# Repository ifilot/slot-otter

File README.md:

# Slot-otter

An 8-bit ISA card for accessing FAT16- or FAT32-formatted SD cards under MS-DOS.

Slot-otter lets a DOS PC use an SD card as an ordinary drive. Fill the card
with files on a modern computer, insert it into your vintage PC, and copy or
run them from DOS.

Both boards are **fully supported and functionally equivalent**: **Slot-otter
Classic** (the original discrete-logic board) and **Slot-otter Forge** (the CPLD
board) use the same OTTERSD driver and
provide the same DOS drive functionality. Owners of the original board can
use the current driver and follow the setup instructions below.

| [Slot-otter Classic](pcb/release/README.md) | [Slot-otter Forge](pcb/cpld/README.md) |
| :---: | :---: |
|  |  |
|  |  |
|  |  |

Click a preview to view the full-resolution image.

[Explore Classic and Forge in the interactive 3D viewer](https://ifilot.github.io/slot-otter/) — rotate and zoom each card in your browser.

A working setup has three parts:

- the **Slot-otter card** in a free 8-bit ISA slot;
- the **OTTERSD driver** on the PC's hard drive, loaded at startup;
- an **SD card** with a FAT16 or FAT32 file system.

## Contents

- [How it works](#how-it-works)
- [Requirements](#requirements)
- [Getting started](#getting-started)
  - [1. Set the port address](#1-set-the-port-address)
  - [2. Download the driver](#2-download-the-driver)
  - [3. Prepare an SD card](#3-prepare-an-sd-card)
  - [4. Install and load OTTERSD](#4-install-and-load-ottersd)
- [Using the card](#using-the-card)
  - [Changing or removing the SD card](#changing-or-removing-the-sd-card)
  - [Freeing memory for games](#freeing-memory-for-games)
  - [Write checks and read-only mode](#write-checks-and-read-only-mode)
  - [Browsing files with Nightwatch](#browsing-files-with-nightwatch)
- [Performance](#performance)
- [Hardware](#hardware)
- [Development](#development)
- [License](#license)

## How it works

`OTTERSD` is the DOS driver for Slot-otter. It is usually started from
`AUTOEXEC.BAT`. It talks to the card over the ISA bus, reads the FAT16 or FAT32
file system on the SD card, and gives the card an ordinary drive letter such
as `S:`. From then on, DIR, COPY, XCOPY, games and other DOS programs use the
card like any other drive and never need to know it is an SD card.

A driver is needed because, on its own, MS-DOS can only use the storage the
PC's BIOS already supports, which means floppy drives and hard disks. Any
other storage device needs a small program that stays in memory and turns DOS
requests such as "open this file" or "list this directory" into commands the
hardware understands. CD-ROM drives are the familiar example. Before a `D:`
drive appears, `CONFIG.SYS` has to load the manufacturer's CD-ROM driver and
`AUTOEXEC.BAT` has to run `MSCDEX`. `OTTERSD` does both of those jobs in a single
program.

## Requirements

Check these before you start. The driver refuses cards or file systems it
cannot handle safely.

- **PC:** an 8088/8086 or later processor and a free 8-bit ISA slot.
- **DOS:** MS-DOS or PC-DOS 3.1 through 6.x.
- **Memory:** about 42 KiB of conventional memory while the driver is loaded.
  No EMS or XMS is needed.
- **SD card:** SDHC or SDXC, at least 501 MiB. Older SDSC cards (2 GB and
  smaller) are not supported.
- **File system:** FAT16 or FAT32 with standard 512-byte sectors on an MBR
  partition. FAT12, exFAT, GPT and extended partitions are not supported.
- **File names:** the usual DOS limit of eight characters for the name and
  three for the extension, such as `DUNE2.EXE`.

## Getting started

Setting up Slot-otter for the first time takes four steps. The first is done
on the card before it goes into the PC, the third on a modern computer, and
the rest under DOS.

1. Set the card's port address and install it in the PC.
2. Download the driver and copy it to the DOS hard drive.
3. Write an empty FAT16 or FAT32 image to an SD card and add your files.
4. Install and load OTTERSD.

### 1. Set the port address

The PC talks to expansion cards through I/O ports, small numbered addresses
that each card listens on. Slot-otter occupies four consecutive ports. The
driver needs to know where they start, and no other card in the PC may use
the same ones.

The base address is set with the 8-position DIP switch labelled **ADDR SEL**
(SW1). Each switch stands for one value. Switches that are ON add their
values together to give the base address; switches that are OFF add nothing.

| Switch | 1 | 2 | 3 | 4 | 5 | 6 | 7 | 8 |
| --- | --- | --- | --- | --- | --- | --- | --- | --- |
| Value (hex) | 200 | 100 | 80 | 40 | 20 | 10 | 8 | 4 |
| **330h** (default) | ON | ON | OFF | OFF | ON | ON | OFF | OFF |
| **300h** | ON | ON | OFF | OFF | OFF | OFF | OFF | OFF |

For example, 330h = 200h + 100h + 20h + 10h, so switches 1, 2, 5 and 6 are ON.
The examples in this README and the driver documentation use 330h. Choose any
free address from 100h to 3FCh. Sound cards often use 330h for their MIDI
port, so pick another address, such as 300h, if your PC has one. Whatever you
choose, pass the same value to the driver with `/PORT:` in
[step 4](#4-install-and-load-ottersd).

With the PC switched off, insert the card into a free 8-bit ISA slot.

### 2. Download the driver

The driver is distributed as a ZIP for copying with a modern PC, as a bare
executable, and as floppy images for PCs that only have a floppy drive. Get
the [latest release](https://github.com/ifilot/slot-otter/releases/latest):

- [OTTERSD-DOS.zip](https://github.com/ifilot/slot-otter/releases/latest/download/OTTERSD-DOS.zip): driver, instructions and license.
- [OTTERSD.EXE](https://github.com/ifilot/slot-otter/releases/latest/download/OTTERSD.EXE): driver executable.
- [floppy_360k.img](https://github.com/ifilot/slot-otter/releases/latest/download/floppy_360k.img): 360 KiB, 5.25-inch DD.
- [floppy_720k.img](https://github.com/ifilot/slot-otter/releases/latest/download/floppy_720k.img): 720 KiB, 3.5-inch DD.
- [floppy_1440k.img](https://github.com/ifilot/slot-otter/releases/latest/download/floppy_1440k.img): 1.44 MiB, 3.5-inch HD.
- [SHA256.TXT](https://github.com/ifilot/slot-otter/releases/latest/download/SHA256.TXT): checksums for checking that downloads are intact.

The floppy images contain the driver, user instructions, a configuration
example and license. They are not boot disks.
Write them to physical floppies or use GoTek,
[BitstreamBeaver](https://github.com/ifilot/bitstream-beaver) or FlashFloppy.

### 3. Prepare an SD card

The easiest way to get a card in the right format is to write one of the
ready-made images to it on a modern PC. Both images contain an **empty,
formatted partition** with no files or folders. After writing one, copy your
files onto the card with the same PC.

**Recommended: [500 MiB FAT16, 16 KiB clusters](https://github.com/ifilot/slot-otter/releases/latest/download/OTTERSD-FAT16-500MiB.zip).**
This gives a useful balance of storage space and write speed. A cluster is
the unit of space the card assigns to a file. Larger clusters mean less
bookkeeping when growing a file, although small files take up more space.

An alternative [500 MiB FAT32 image with 4 KiB clusters](https://github.com/ifilot/slot-otter/releases/latest/download/OTTERSD-FAT32-500MiB.zip)
is also available.

Extract the ZIP and write its IMG to the **entire card**. This replaces existing
partitions and files: back up first and select the correct device. Do not copy
the IMG as a file or reformat the card afterwards. The image occupies 501 MiB,
including a small area before the 500 MiB partition. On a larger card, the
remaining space is unused by this image. These images hold your files; they
do not boot DOS.

A card that is already formatted FAT16 or FAT32 and meets the
[requirements](#requirements) can also be used without writing an image.

### 4. Install and load OTTERSD

The driver is copied to the hard drive and started like any other DOS program.
It must not be loaded from the SD drive it provides.

Copy OTTERSD.EXE to a directory on your DOS hard drive, such as `C:\OTTERSD`.
Choose an unused drive letter; this example uses `S:`. Add `LASTDRIVE=S` to
CONFIG.SYS (or keep an existing value of S or later), then reboot, insert the
SD card and load:

```dos
C:\OTTERSD\OTTERSD /DRIVE:S /PORT:330 /RW
```

The DOS screenshots on this page are illustrative drafts using the driver's
messages. Timing and resident-memory figures are examples, not hardware measurements.
The driver prints its version and a message before lengthy work. Console
commands also show percentage progress while comparing FAT copies; wait for
the final success message before using or removing the card. Redirected
output keeps plain status messages without the animated percentage.

`/PORT:330` must match the DIP-switch setting from
[step 1](#1-set-the-port-address). `/RW` enables writing with read-back checks.
Omit it or use `/RO` for read-only access. Once the driver reports that the
card is mounted, you can use commands such as `DIR S:\`.

Add the loading command to AUTOEXEC.BAT if you want it to run at startup.
Run OTTERSD as a program; do not add it as a `DEVICE=` line in CONFIG.SYS.
See the [installation guide](driver/docs/INSTALLATION.md) for the full setup
and available options.

## Using the card

Once loaded, the SD drive behaves like any other DOS drive. A few things
differ from a fixed hard disk, mainly because the card can be removed and the
driver can be unloaded.

### Changing or removing the SD card

**Always unmount before removing a card, and mount again after inserting one.**
Treat this like safely ejecting a card on your modern PC. DOS programs and
the driver can keep file data and information about the card in memory.
Removing or swapping a mounted card can lose changes or cause the driver
to use information belonging to the previous card, risking file corruption.

1. Finish copying and close any programs using the SD card. Return to a
   drive other than the SD card, such as `C:`.
2. Run `C:\OTTERSD\OTTERSD /UNMOUNT`. **Wait for it to succeed before
   removing the card.** If it reports an error, leave the card inserted
   and resolve the error first.
3. Remove the card and insert the card you want to use.
4. Run `C:\OTTERSD\OTTERSD /MOUNT` and wait for it to succeed before
   accessing the SD drive again.

Follow these steps even when reinserting the same card, especially after
changing its contents on another computer. Unmounting leaves the driver
loaded, so you do not need to reboot to change cards.

| Unmount before removing the card | Mount after inserting the card |
| :---: | :---: |
|  |  |

### Freeing memory for games

Some games need every kilobyte of conventional memory. The driver can be
removed from memory without rebooting: close programs using the SD card,
switch to your hard drive and run `C:\OTTERSD\OTTERSD /UNLOAD`. Run the
loading command again to bring the SD drive back.

### Write checks and read-only mode

With `/RW`, every block written to the card is read back and checked before
the write is reported as successful. With `/RO`, or without either option,
the card is mounted read-only and nothing on it can be changed. The access
mode is fixed when the driver is loaded; reboot to change it.

### Browsing files with Nightwatch

For browsing and copying files, we recommend
[Nightwatch](https://github.com/ifilot/nightwatch) together with OTTERSD.
Nightwatch is a separate project and is not bundled in these downloads.

## Performance

File-copy tests on an **80286 running at 20 MHz** gave these results:

| Direction | FAT16 card | FAT32 card |
| --- | --- | --- |
| To the SD card | 15 KiB/s | 10 KiB/s |
| From the SD card | 38 KiB/s | 38 KiB/s |

These are measured file-transfer speeds, not guaranteed speeds for every
system or card. FAT16 was faster when writing in these tests; reading was
equally fast with both formats. Speeds also depend on the CPU, the ISA bus
and the disk being copied to or from.

## Hardware

Slot-otter has two supported, functionally equivalent board designs:
the [Slot-otter Classic](pcb/release/README.md) discrete-logic board and
[Slot-otter Forge](pcb/cpld/README.md) CPLD board. Both use the same OTTERSD driver,
I/O port settings and SD card formats, including read and write support.

Classic implements the interface with discrete logic chips.
On Forge, an ATF1504AS implements the interface logic, with an external 74HCT688
comparing address lines A2 to A9 against the DIP-switch setting.

The hardware documentation includes KiCad sources, the bill of materials,
assembly positions, fabrication files and CPLD programming instructions.
Review the manufacturing reports, bring-up checks and timing limits before
building or using this revision.

Use the hardware files for your board: Classic and Forge have
different fabrication files and pinouts. The earlier
[prototype sources](pcb/prototype/README.md) are also retained.

## Development

The [driver documentation](driver/README.md) covers the source code, build
instructions and regression tests. The driver is built with Turbo C 2.0 and
TASM 2. [DOSBox-VirtIsa](https://github.com/ifilot/dosbox-virtisa) provides an
emulated ISA interface for development and testing.

See the [release history](CHANGELOG.md) for changes between versions.

## License

Slot-otter is certified open source hardware by the
[Open Source Hardware Association](https://certification.oshwa.org/nl000046.html)
under UID NL000046.

Project-authored hardware and mechanical designs use CERN-OHL-S-2.0;
software and CPLD logic use GPL-3.0-or-later; documentation uses CC-BY-SA-4.0.
See [licensing scope and full texts](LICENSE.md) for details and third-party
exceptions. Bundled Borland tools retain their proprietary terms.

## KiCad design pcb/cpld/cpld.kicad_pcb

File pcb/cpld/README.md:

# Slot-otter Forge

Forge is the CPLD-based Slot-otter board. Revision 1.0 uses an ATF1504AS
in a PLCC44 socket and the reassigned pinout in [logic/README.txt](logic/README.txt).
Do not use this programming image with an earlier PCB pinout.

## Design sources and licenses

Open `cpld.kicad_pro` in KiCad 10. The schematic is `cpld.kicad_sch` and the
PCB is `cpld.kicad_pcb`. Project libraries are registered through `fp-lib-table`
and `sym-lib-table`, with their files under `components/`.

Project-authored hardware uses CERN-OHL-S-2.0, software and CPLD logic use
GPL-3.0-or-later, and documentation uses CC-BY-SA-4.0. See the repository
[licensing statement](../../LICENSE.md) and [full license texts](../../LICENSES/).
The source location is https://github.com/ifilot/slot-otter .

The original discrete-logic board, [Slot-otter Classic](../release/README.md), remains fully supported
and is functionally equivalent to this board, using the same OTTERSD driver
and setup instructions. Its component references, manufacturing files and
pinouts differ from this board's. The earlier
[prototype sources](../prototype/README.md) are also retained.

## Manufacturing and assembly

- [Schematic PDF](cpld.pdf) and [SVG](cpld.svg).
- [Bill of materials](production/bom.csv), including schematic supplier fields and datasheet links.
- [Placement positions](production/positions.csv), in millimetres, and [assembly references](production/designators.csv).
- [Gerbers and drill files](GERBERS/), also available as a [fabrication ZIP](GERBERS/cpld.zip).
- [Generation manifest](production/manifest.json), [DRC](production/drc.json) and [ERC](production/erc.json).

Check `manufacturing_ready` and the reports before ordering. A generated export
is not manufacturing approval. A supplier field copied from the schematic is
not a purchasing validation; verify the exact package and part before assembly.
U1 needs both the ATF1504AS PLCC44 device and a compatible through-hole
PLCC44 socket. J2 is the integral ISA edge connector, not a separately
purchased connector. The bracket [STL sources](../../bracket/README.md) were authored as meshes for
earlier cards; check mechanical fit before using them with the CPLD layout.

Regenerate the outputs with KiCad 10 installed:

```sh
python3 pcb/cpld/export.py
```

Use `--kicad-cli /path/to/kicad-cli` when the executable is not on PATH.
The exporter refills and saves PCB copper zones, runs DRC/ERC, exports the
current schematic and board, rebuilds the fabrication ZIP, and records source
hashes. It exports both board sides in the placement CSV; configure your assembler's origin and rotation
conventions before submitting it. The `.dsn` and `.ses` files are historical
routing snapshots, not revision 1.0 manufacturing inputs.

## CPLD build and bring-up

The [CUPL source](logic/slototter.pld), [build script](logic/build.cmd),
[functional-vector generator](logic/generate_vectors.py) and
[pinout and timing documentation](logic/README.txt) are the editable logic sources.
Run `logic/build.cmd test` on Windows with WinCUPL installed to compile, fit and
simulate; then run `logic/build.cmd` for an image without simulation vectors.
Generated programming files are under `logic/build/` and are ignored by Git.

The revision 1.0 board has no on-board JTAG connector; its JTAG pads are
unconnected. Program the CPLD in a compatible external PLCC44 adapter or
fixture before inserting it into U1's socket. Use a programmer supporting
ATF1504AS and the target's voltage; follow its adapter pinout and power
instructions. The reserved PLCC44 JTAG pins are 7 TDI, 13 TMS, 32 TCK and
38 TDO. Program the newly generated `logic/build/slototter.jed`, then use
the programmer's verify operation. Programmer-specific commands depend on
the selected programmer. Disconnect power before inserting or removing U1.
Follow the bring-up checks and timing limits in the logic
README before using the [DOS driver](../../driver/README.md) on this revision.

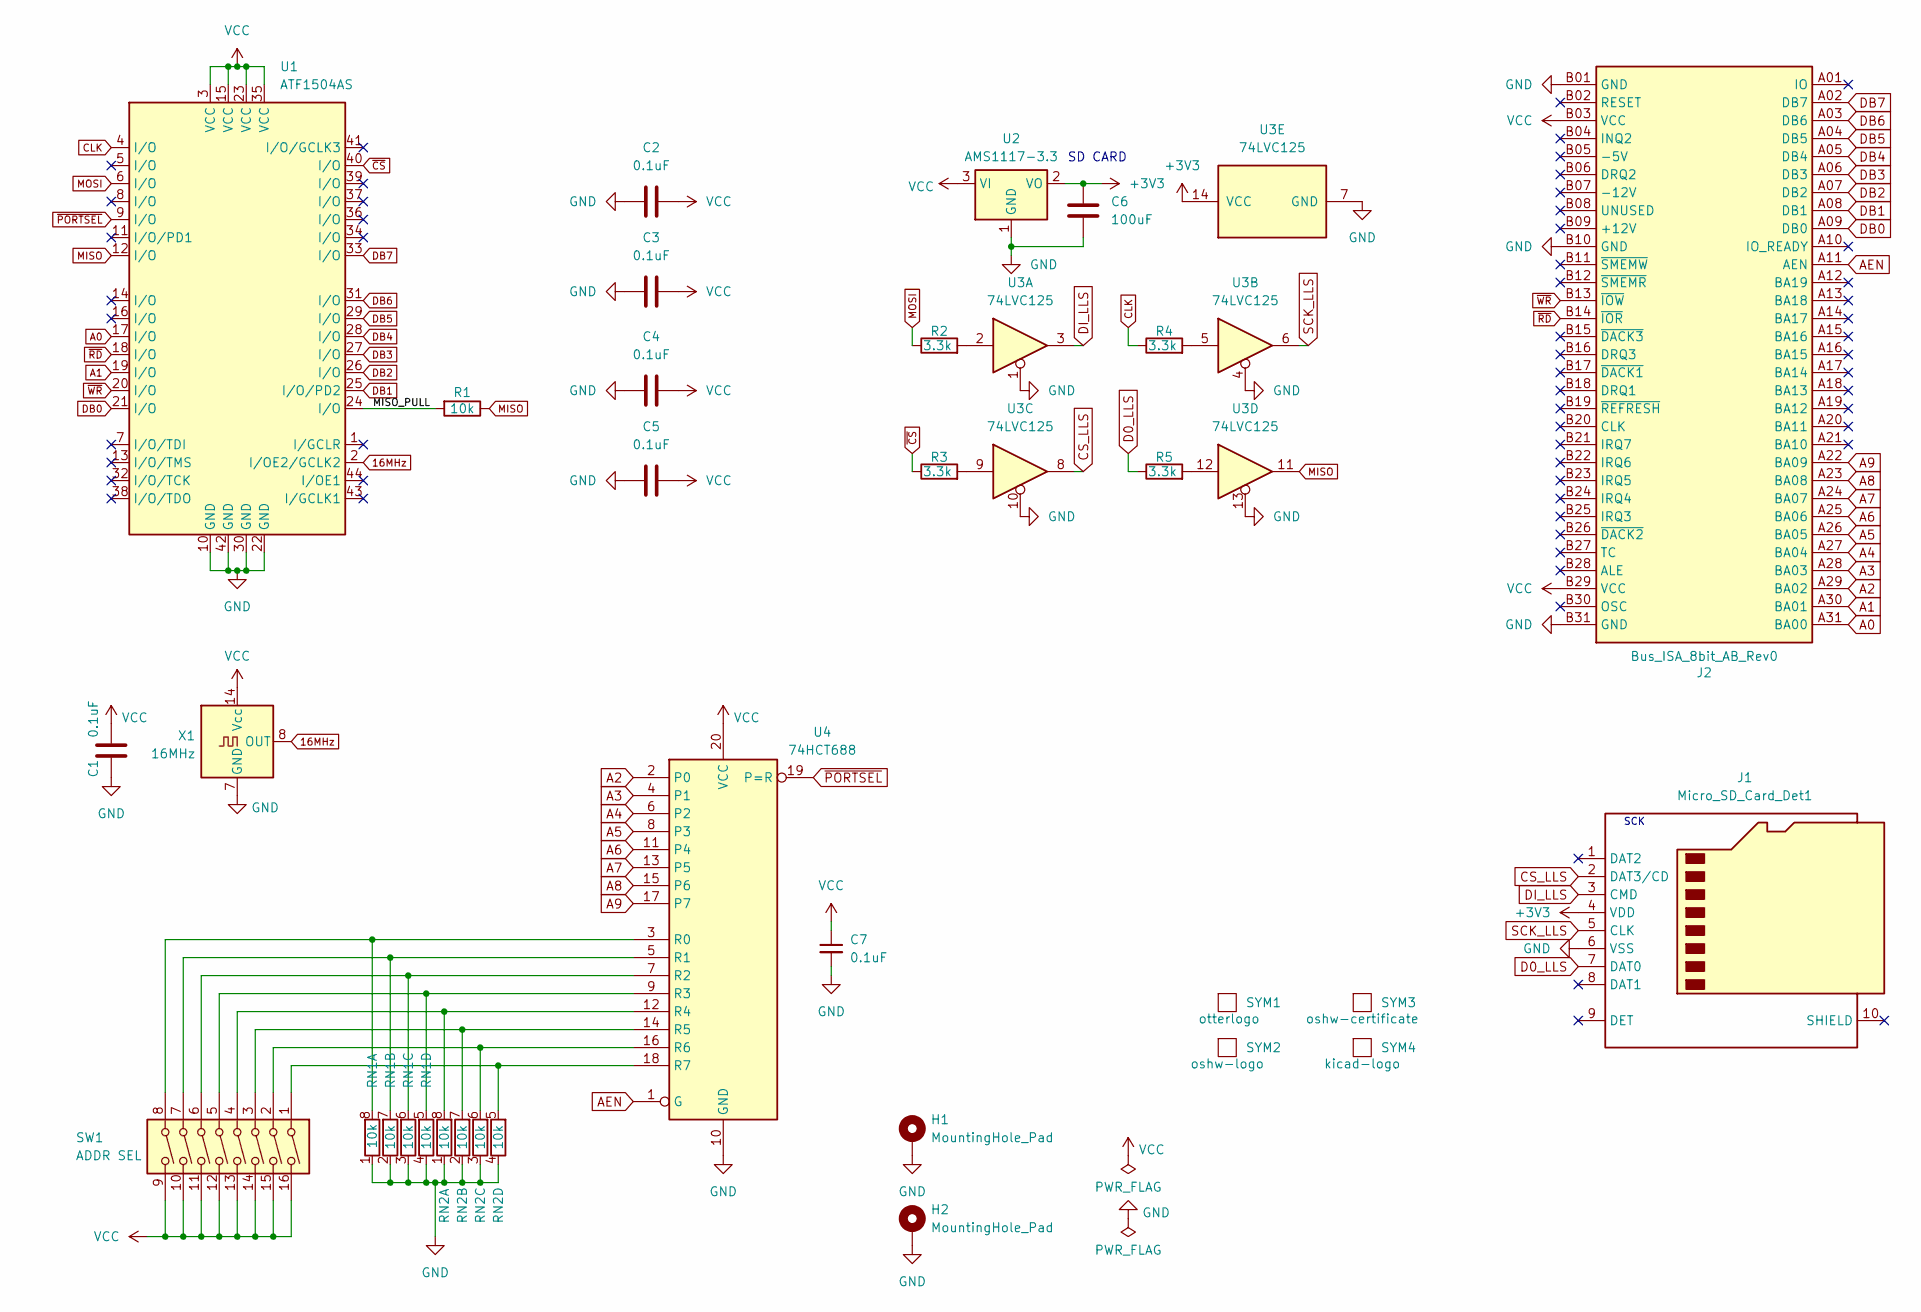
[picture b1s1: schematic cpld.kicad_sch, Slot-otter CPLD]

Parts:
C1, C7: 0.1uF; C_0805_2012Metric; LCSC C126469
C2, C3, C4, C5: 0.1uF; C_0805_2012Metric
C6: 100uF; C_1206_3216Metric_Pad1.33x1.80mm_HandSolder; LCSC C309030
H1, H2: MountingHole_Pad; MountingHole_3.2mm_M3_DIN965_Pad_TopBottom
J1: Micro_SD_Card_Det1; CONN9_MSD-1_CUD; LCSC C381082
J2: Bus_ISA_8bit_AB_Rev0; ISA_CARD_EDGE_CONNECTOR_8BIT_Rev1
R1: 10k; R_0805_2012Metric; LCSC C5159708
R2, R3, R4, R5: 3.3k; R_0805_2012Metric_Pad1.20x1.40mm_HandSolder; LCSC C407459
RN1, RN2: 10k; R_Array_Convex_4x0612; LCSC C29718
SW1: ADDR SEL; SW_DIP_SPSTx08_Slide_9.78x22.5mm_W7.62mm_P2.54mm
SYM1: otterlogo; slototter-logo-v2_h12
SYM2: oshw-logo; OSHW-Logo_7.5x8mm_SilkScreen
SYM3: oshw-certificate; oshwa_h15
SYM4: kicad-logo; KiCad-Logo2_5mm_SilkScreen
U1: ATF1504AS; PLCC-44_THT-Socket
U2: AMS1117-3.3; SOT-223-3_TabPin2; LCSC C5346136
U3: 74LVC125; TSSOP-14_4.4x5mm_P0.65mm; LCSC C7494906
U4: 74HCT688; SOIC-20W_7.5x12.8mm_P1.27mm; LCSC C2649422
X1: 16MHz; Oscillator_DIP-14

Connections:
16MHz: U1.2 (I/OE2/GCLK2), X1.8 (OUT)
+3V3: C6.1, J1.4 (VDD), U2.2 (VO), U3.14 (VCC)
/MISO_PULL: R1.2, U1.24 (I/O)
A0: J2.A31 (BA00), U1.17 (I/O)
A1: J2.A30 (BA01), U1.19 (I/O)
A2: J2.A29 (BA02), U4.2 (P0)
A3: J2.A28 (BA03), U4.4 (P1)
A4: J2.A27 (BA04), U4.6 (P2)
A5: J2.A26 (BA05), U4.8 (P3)
A6: J2.A25 (BA06), U4.11 (P4)
A7: J2.A24 (BA07), U4.13 (P5)
A8: J2.A23 (BA08), U4.15 (P6)
A9: J2.A22 (BA09), U4.17 (P7)
AEN: J2.A11 (AEN), U4.1 (G)
CLK: R4.1, U1.4 (I/O)
CS_LLS: J1.2 (DAT3/CD), U3.8
D0_LLS: J1.7 (DAT0), R5.1
DB0: J2.A09 (DB0), U1.21 (I/O)
DB1: J2.A08 (DB1), U1.25 (I/O/PD2)
DB2: J2.A07 (DB2), U1.26 (I/O)
DB3: J2.A06 (DB3), U1.27 (I/O)
DB4: J2.A05 (DB4), U1.28 (I/O)
DB5: J2.A04 (DB5), U1.29 (I/O)
DB6: J2.A03 (DB6), U1.31 (I/O)
DB7: J2.A02 (DB7), U1.33 (I/O)
DI_LLS: J1.3 (CMD), U3.3
GND: C1.1, C2.2, C3.2, C4.2, C5.2, C6.2, C7.2, H1.1 (1_1), H2.1 (1_1), J1.6 (VSS), J2.B01 (GND), J2.B10 (GND), J2.B31 (GND), RN1.1 (R1.1), RN1.2 (R2.1), RN1.3 (R3.1), RN1.4 (R4.1), RN2.1 (R1.1), RN2.2 (R2.1), RN2.3 (R3.1), RN2.4 (R4.1), U1.10 (GND), U1.22 (GND), U1.30 (GND), U1.42 (GND), U2.1 (GND), U3.1, U3.4, U3.7 (GND), U3.10, U3.13, U4.10 (GND), X1.7 (GND)
MISO: R1.1, U1.12 (I/O), U3.11
MOSI: R2.1, U1.6 (I/O)
unnamed: R2.2, U3.2
unnamed: R3.2, U3.9
unnamed: R4.2, U3.5
unnamed: R5.2, U3.12
unnamed: RN1.8 (R1.2), SW1.8, U4.3 (R0)
unnamed: RN1.7 (R2.2), SW1.7, U4.5 (R1)
unnamed: RN1.6 (R3.2), SW1.6, U4.7 (R2)
unnamed: RN1.5 (R4.2), SW1.5, U4.9 (R3)
unnamed: RN2.8 (R1.2), SW1.4, U4.12 (R4)
unnamed: RN2.7 (R2.2), SW1.3, U4.14 (R5)
unnamed: RN2.6 (R3.2), SW1.2, U4.16 (R6)
unnamed: RN2.5 (R4.2), SW1.1, U4.18 (R7)
SCK_LLS: J1.5 (CLK), U3.6
VCC: C1.2, C2.1, C3.1, C4.1, C5.1, C7.1, J2.B03 (VCC), J2.B29 (VCC), SW1.9, SW1.10, SW1.11, SW1.12, SW1.13, SW1.14, SW1.15, SW1.16, U1.3 (VCC), U1.15 (VCC), U1.23 (VCC), U1.35 (VCC), U2.3 (VI), U4.20 (VCC), X1.14 (Vcc)
~CS: R3.1, U1.40 (I/O)
~PORTSEL: U1.9 (I/O), U4.19 (P=R)
~RD: J2.B14 (~IOR), U1.18 (I/O)
~WR: J2.B13 (~IOW), U1.20 (I/O)

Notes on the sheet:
SCK
SD CARD

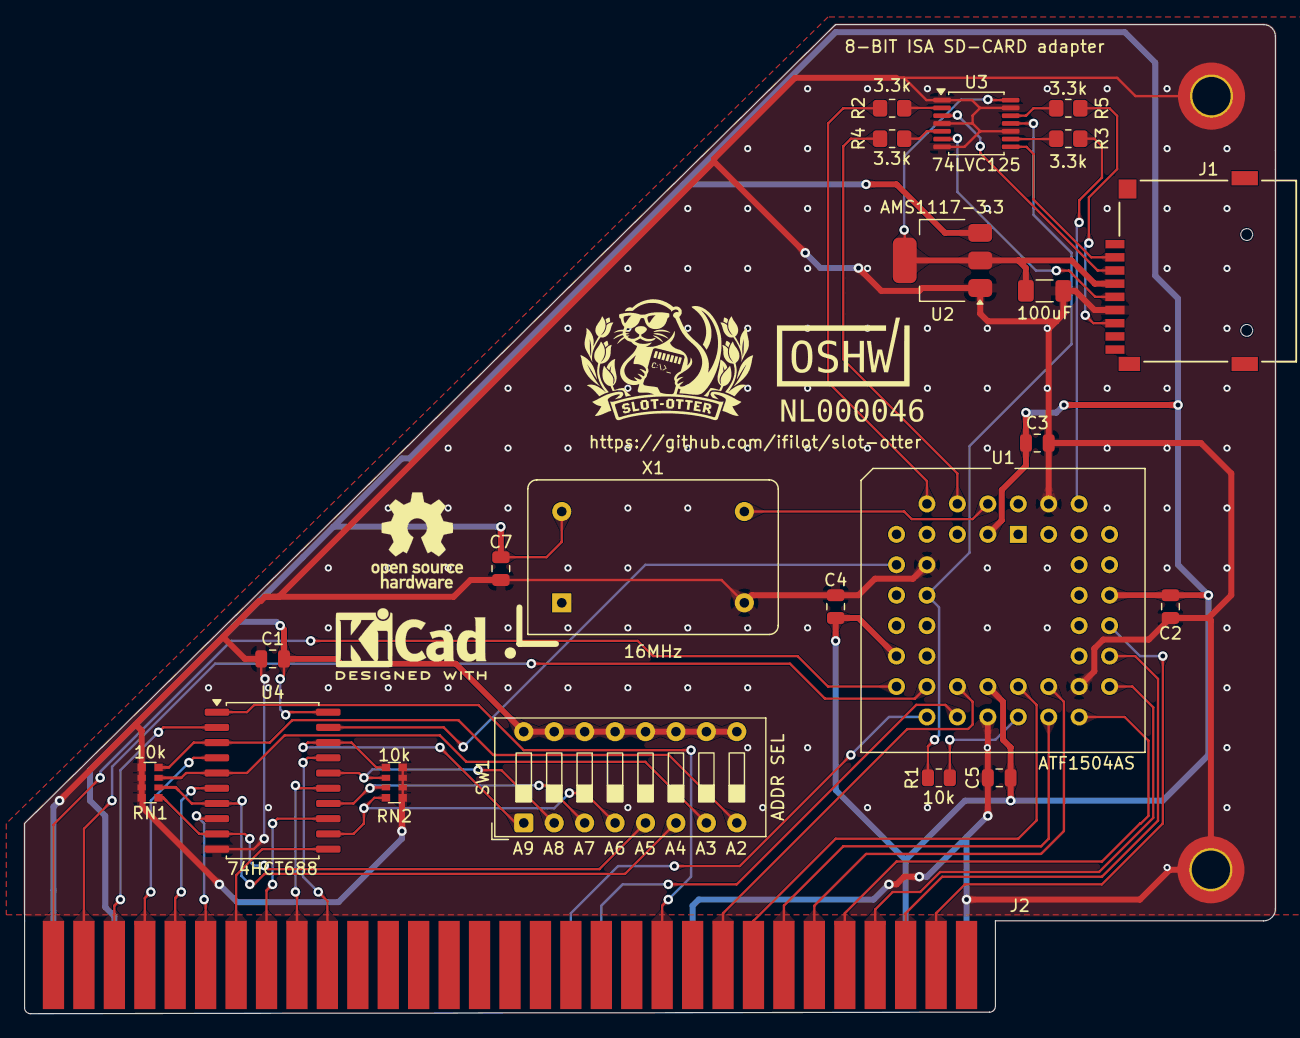
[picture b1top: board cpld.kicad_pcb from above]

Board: 2 copper layers, 104.4 x 82.5 mm, 28 parts (0 on the bottom side), 47 nets.

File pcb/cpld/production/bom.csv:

"Designator","Footprint","Quantity","Value","LCSC Part #","Datasheet"
"C1-C5,C7","Capacitor_SMD:C_0805_2012Metric","6","0.1uF","",""
"C6","Capacitor_SMD:C_1206_3216Metric_Pad1.33x1.80mm_HandSolder","1","100uF","",""
"J1","components:CONN9_MSD-1_CUD","1","Micro_SD_Card_Det1","","https://datasheet.lcsc.com/lcsc/2110151630_XKB-Connectivity-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"
"J2","components:ISA_CARD_EDGE_CONNECTOR_8BIT_Rev1","1","Bus_ISA_8bit_AB_Rev0","","https://en.wikipedia.org/wiki/Industry_Standard_Architecture"
"R1","Resistor_SMD:R_0805_2012Metric","1","10k","",""
"R2-R5","Resistor_SMD:R_0805_2012Metric_Pad1.20x1.40mm_HandSolder","4","3.3k","",""
"RN1,RN2","Resistor_SMD:R_Array_Convex_4x0612","2","10k","",""
"SW1","Button_Switch_THT:SW_DIP_SPSTx08_Slide_9.78x22.5mm_W7.62mm_P2.54mm","1","ADDR SEL","",""
"U1","Package_LCC:PLCC-44_THT-Socket","1","ATF1504AS","","https://ww1.microchip.com/downloads/en/DeviceDoc/ATF1504AS(L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"
"U2","Package_TO_SOT_SMD:SOT-223-3_TabPin2","1","AMS1117-3.3","","http://www.advanced-monolithic.com/pdf/ds1117.pdf"
"U3","Package_SO:TSSOP-14_4.4x5mm_P0.65mm","1","74LVC125","","http://www.ti.com/lit/gpn/sn74LVC125"
"U4","Package_SO:SOIC-20W_7.5x12.8mm_P1.27mm","1","74HCT688","","https://www.ti.com/lit/ds/symlink/cd54hc688.pdf"
"X1","Oscillator:Oscillator_DIP-14","1","16MHz","","http://www.golledge.com/pdf/products/tcxos/gtxos14.pdf"

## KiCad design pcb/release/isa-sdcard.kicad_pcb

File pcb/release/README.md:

# Slot-otter Classic

Classic is the original discrete-logic Slot-otter board. It remains fully supported
and is functionally equivalent to [Slot-otter Forge](../cpld/README.md),
the CPLD-based board. Both boards use the same
OTTERSD driver, I/O port settings and SD card formats, with read and write
support. Follow the [main setup instructions](../../README.md#getting-started)
with either board.

This directory contains the Classic hardware sources. Use the matching
source revision when repairing or reproducing a card; these fabrication files
and pinouts differ from Forge's. See the
[Blender render instructions](render/README.md) to reproduce the image.

Project-authored hardware remains available under CERN-OHL-S-2.0 and this
documentation under CC-BY-SA-4.0; see [licensing scope](../../LICENSE.md).

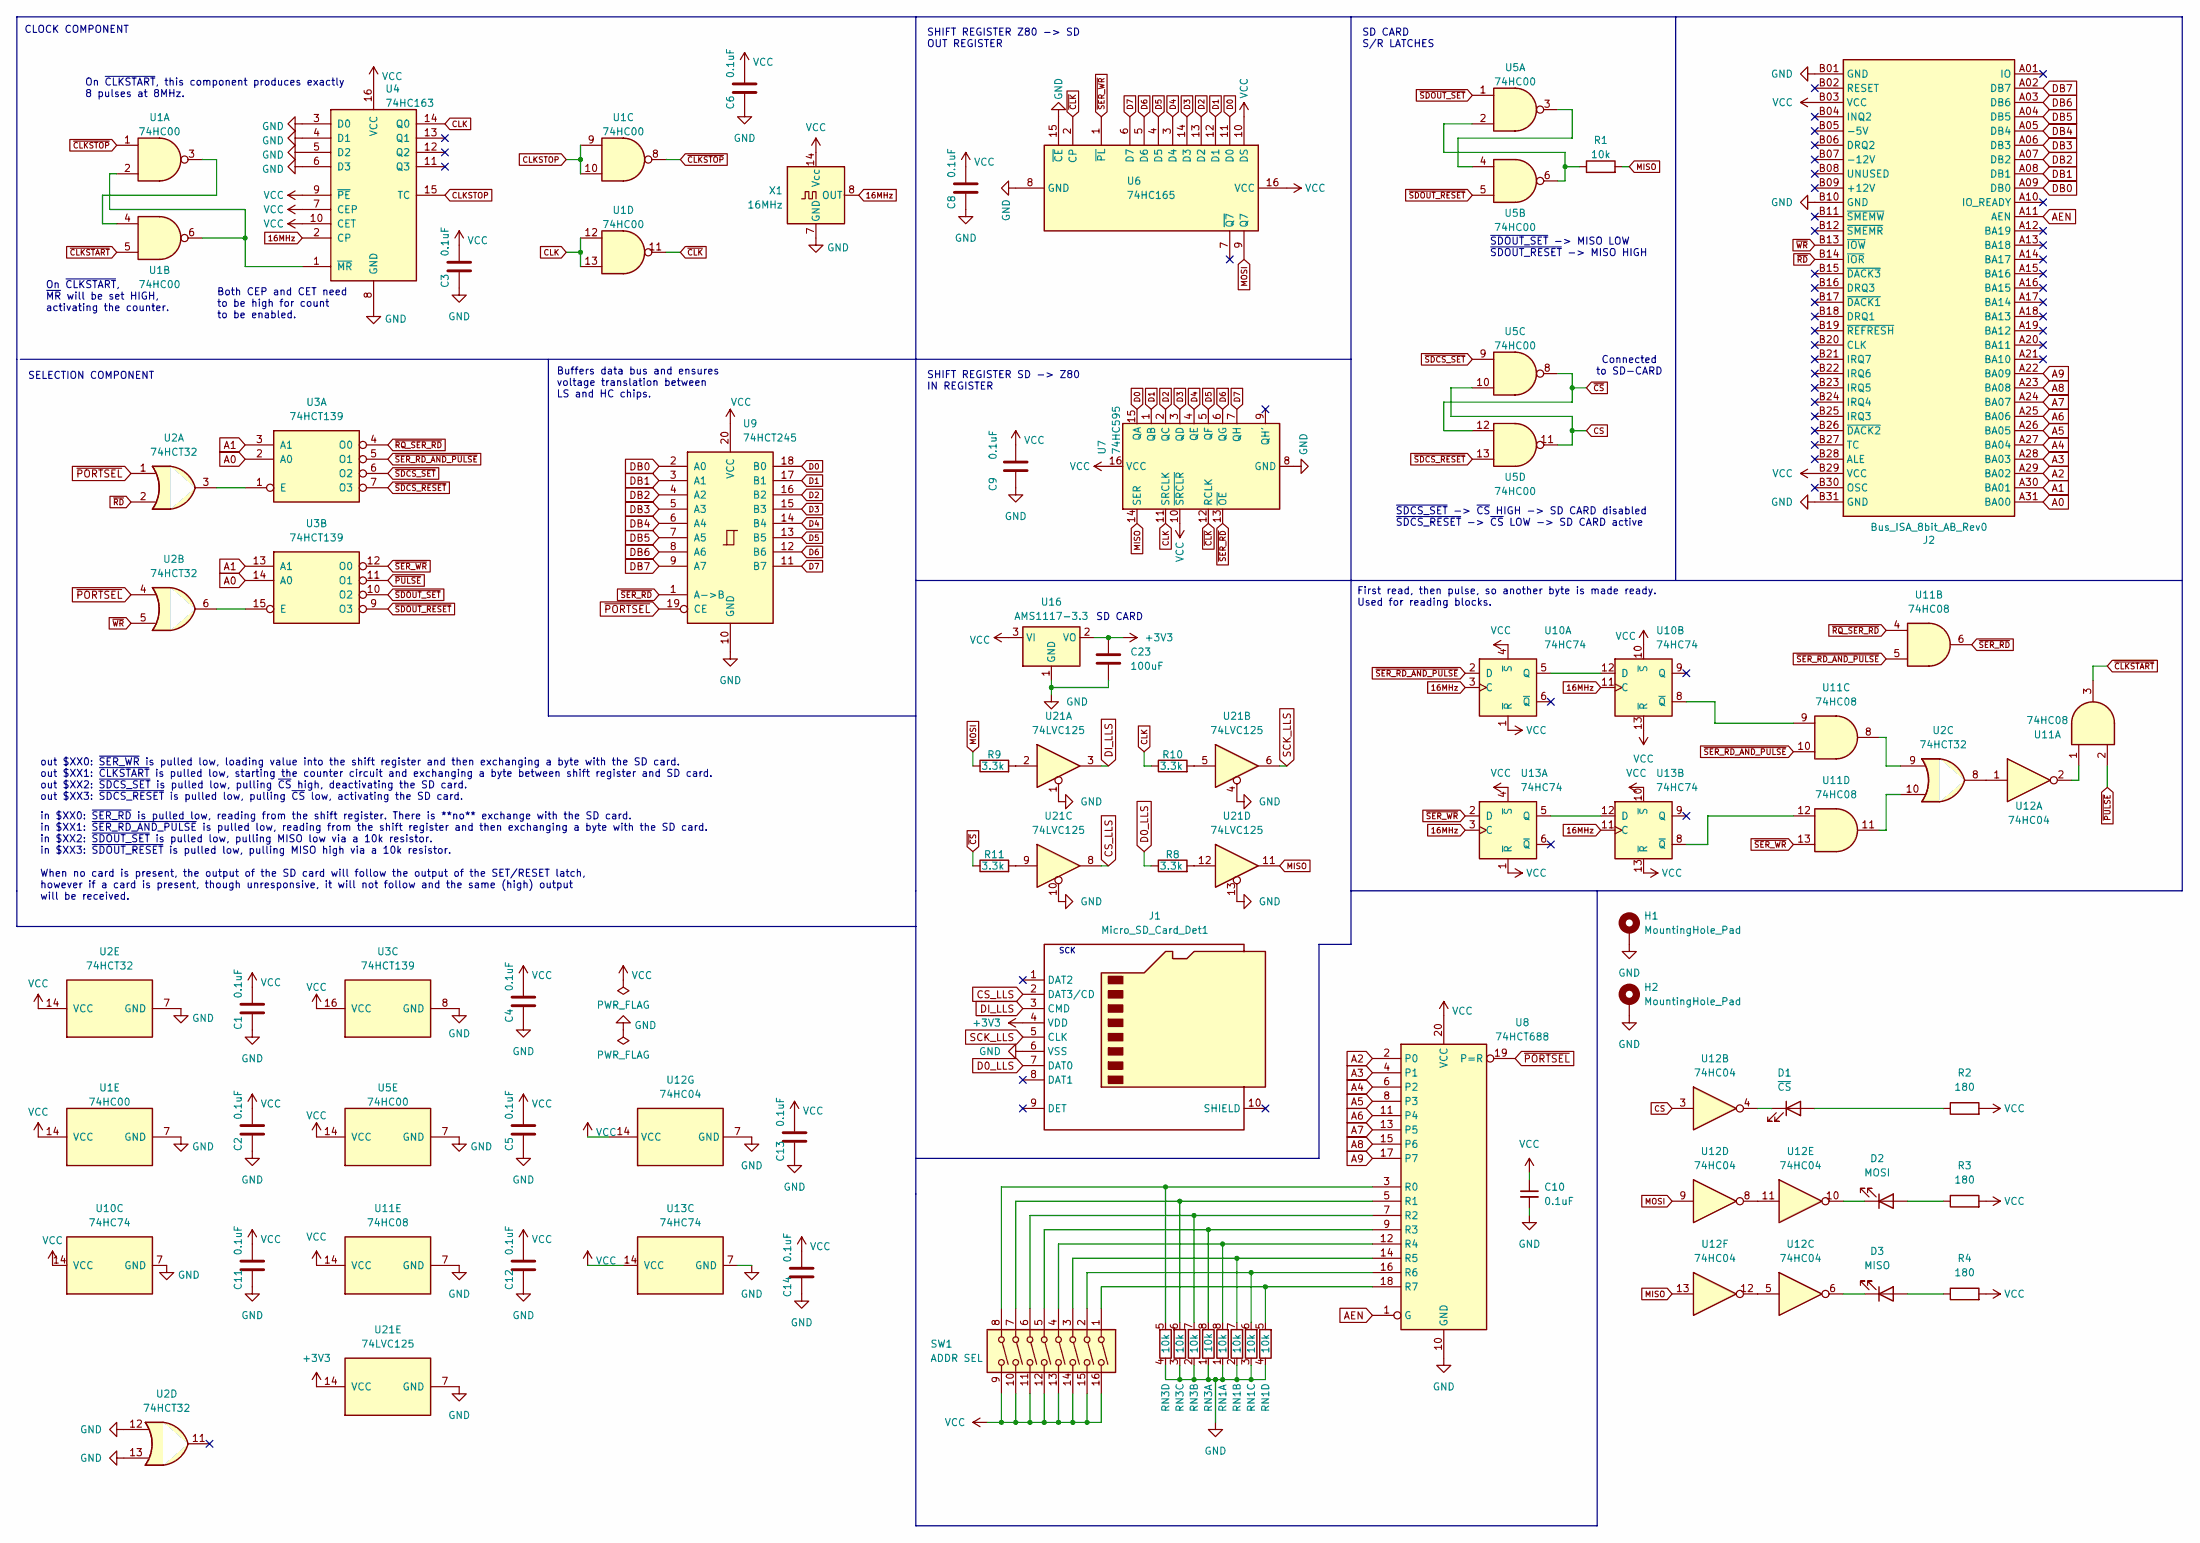
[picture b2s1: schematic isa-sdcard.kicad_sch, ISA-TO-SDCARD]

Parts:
C1, C2, C3, C4, C5, C6, C8, C9, C10, C11, C12, C13, C14: 0.1uF; C_0805_2012Metric; LCSC C126469
C23: 100uF; C_1206_3216Metric_Pad1.33x1.80mm_HandSolder; LCSC C309030
D1: ~{CS}; LED_0805_2012Metric; LCSC C84256
D2: MOSI; LED_0805_2012Metric; LCSC C84256
D3: MISO; LED_0805_2012Metric; LCSC C84256
H1, H2: MountingHole_Pad; MountingHole_3.2mm_M3_DIN965_Pad_TopBottom
J1: Micro_SD_Card_Det1; CONN9_MSD-1_CUD; LCSC C381082
J2: Bus_ISA_8bit_AB_Rev0; ISA_CARD_EDGE_CONNECTOR_8BIT_Rev1
R1: 10k; R_0805_2012Metric; LCSC C5159708
R2, R3, R4: 180; R_0805_2012Metric; LCSC C17540
R8, R9, R10, R11: 3.3k; R_0805_2012Metric_Pad1.20x1.40mm_HandSolder; LCSC C407459
RN1, RN3: 10k; R_Array_Convex_4x0612; LCSC C29718
SW1: ADDR SEL; SW_DIP_SPSTx08_Slide_9.78x22.5mm_W7.62mm_P2.54mm
U1, U5: 74HC00; SOIC-14_3.9x8.7mm_P1.27mm; LCSC C699445
U2: 74HCT32; SOIC-14_3.9x8.7mm_P1.27mm; LCSC C5985
U3: 74HCT139; SOIC-16_3.9x9.9mm_P1.27mm; LCSC C545677
U4: 74HC163; SOIC-16_3.9x9.9mm_P1.27mm; LCSC C338758
U6: 74HC165; SOIC-16_3.9x9.9mm_P1.27mm; LCSC C5613
U7: 74HC595; SOIC-16_3.9x9.9mm_P1.27mm; LCSC C5947
U8: 74HCT688; SOIC-20W_7.5x12.8mm_P1.27mm; LCSC C2649422
U9: 74HCT245; SOIC-20W_7.5x12.8mm_P1.27mm; LCSC C5979
U10, U13: 74HC74; SOIC-14_3.9x8.7mm_P1.27mm; LCSC C6762
U11: 74HC08; SOIC-14_3.9x8.7mm_P1.27mm; LCSC C5593
U12: 74HC04; SOIC-14_3.9x8.7mm_P1.27mm; LCSC C5590
U16: AMS1117-3.3; SOT-223-3_TabPin2; LCSC C5346136
U21: 74LVC125; TSSOP-14_4.4x5mm_P0.65mm; LCSC C7494906
X1: 16MHz; Oscillator_DIP-14

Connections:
16MHz: U4.2 (CP), U10.3 (C), U10.11 (C), U13.3 (C), U13.11 (C), X1.8 (OUT)
+3V3: C23.1, J1.4 (VDD), U16.2 (VO), U21.14 (VCC)
A0: J2.A31 (BA00), U3.2 (A0), U3.14 (A0)
A1: J2.A30 (BA01), U3.3 (A1), U3.13 (A1)
A2: J2.A29 (BA02), U8.2 (P0)
A3: J2.A28 (BA03), U8.4 (P1)
A4: J2.A27 (BA04), U8.6 (P2)
A5: J2.A26 (BA05), U8.8 (P3)
A6: J2.A25 (BA06), U8.11 (P4)
A7: J2.A24 (BA07), U8.13 (P5)
A8: J2.A23 (BA08), U8.15 (P6)
A9: J2.A22 (BA09), U8.17 (P7)
AEN: J2.A11 (AEN), U8.1 (G)
CLK: R10.1, U1.12, U1.13, U4.14 (Q0), U7.11 (SRCLK)
CLKSTOP: U1.9, U1.10, U4.15 (TC)
CS: U5.10, U5.11, U12.3
CS_LLS: J1.2 (DAT3/CD), U21.8
D0: U6.11 (D0), U7.15 (QA), U9.18 (B0)
D0_LLS: J1.7 (DAT0), R8.1
D1: U6.12 (D1), U7.1 (QB), U9.17 (B1)
D2: U6.13 (D2), U7.2 (QC), U9.16 (B2)
D3: U6.14 (D3), U7.3 (QD), U9.15 (B3)
D4: U6.3 (D4), U7.4 (QE), U9.14 (B4)
D5: U6.4 (D5), U7.5 (QF), U9.13 (B5)
D6: U6.5 (D6), U7.6 (QG), U9.12 (B6)
D7: U6.6 (D7), U7.7 (QH), U9.11 (B7)
DB0: J2.A09 (DB0), U9.2 (A0)
DB1: J2.A08 (DB1), U9.3 (A1)
DB2: J2.A07 (DB2), U9.4 (A2)
DB3: J2.A06 (DB3), U9.5 (A3)
DB4: J2.A05 (DB4), U9.6 (A4)
DB5: J2.A04 (DB5), U9.7 (A5)
DB6: J2.A03 (DB6), U9.8 (A6)
DB7: J2.A02 (DB7), U9.9 (A7)
DI_LLS: J1.3 (CMD), U21.3
GND: C1.1, C2.1, C3.1, C4.1, C5.1, C6.1, C8.1, C9.1, C10.2, C11.1, C12.1, C13.1, C14.1, C23.2, H1.1, H2.1, J1.6 (VSS), J2.B01 (GND), J2.B10 (GND), J2.B31 (GND), RN1.1 (R1.1), RN1.2 (R2.1), RN1.3 (R3.1), RN1.4 (R4.1), RN3.1 (R1.1), RN3.2 (R2.1), RN3.3 (R3.1), RN3.4 (R4.1), U1.7 (GND), U2.7 (GND), U2.12, U2.13, U3.8 (GND), U4.3 (D0), U4.4 (D1), U4.5 (D2), U4.6 (D3), U4.8 (GND), U5.7 (GND), U6.8 (GND), U6.15 (~CE), U7.8 (GND), U8.10 (GND), U9.10 (GND), U10.7 (GND), U11.7 (GND), U12.7 (GND), U13.7 (GND), U16.1 (GND), U21.1, U21.4, U21.7 (GND), U21.10, U21.13, X1.7 (GND)
MISO: R1.2, U7.14 (SER), U12.13, U21.11
MOSI: R9.1, U6.9 (Q7), U12.9
unnamed: D1.2 (A), R2.1
unnamed: D1.1 (K), U12.4
unnamed: D2.2 (A), R3.1
unnamed: D2.1 (K), U12.10
unnamed: D3.2 (A), R4.1
unnamed: D3.1 (K), U12.6
unnamed: R1.1, U5.2, U5.6
unnamed: R8.2, U21.12
unnamed: R9.2, U21.2
unnamed: R10.2, U21.5
unnamed: R11.2, U21.9
unnamed: RN1.8 (R1.2), SW1.4, U8.12 (R4)
unnamed: RN1.7 (R2.2), SW1.3, U8.14 (R5)
unnamed: RN1.6 (R3.2), SW1.2, U8.16 (R6)
unnamed: RN1.5 (R4.2), SW1.1, U8.18 (R7)
unnamed: RN3.8 (R1.2), SW1.5, U8.9 (R3)
unnamed: RN3.7 (R2.2), SW1.6, U8.7 (R2)
unnamed: RN3.6 (R3.2), SW1.7, U8.5 (R1)
unnamed: RN3.5 (R4.2), SW1.8, U8.3 (R0)
unnamed: U1.3, U1.4
unnamed: U2.3, U3.1 (E)
unnamed: U2.6, U3.15 (E)
unnamed: U1.2, U1.6, U4.1 (~MR)
unnamed: U5.3, U5.4
unnamed: U10.5 (Q), U10.12 (D)
unnamed: U10.8 (~Q), U11.9
unnamed: U11.1, U12.2
unnamed: U2.9, U11.8
unnamed: U2.10, U11.11
unnamed: U2.8, U12.1
unnamed: U12.8, U12.11
unnamed: U12.5, U12.12
unnamed: U13.5 (Q), U13.12 (D)
unnamed: U11.12, U13.8 (~Q)
SCK_LLS: J1.5 (CLK), U21.6
VCC: C1.2, C2.2, C3.2, C4.2, C5.2, C6.2, C8.2, C9.2, C10.1, C11.2, C12.2, C13.2, C14.2, J2.B03 (VCC), J2.B29 (VCC), R2.2, R3.2, R4.2, SW1.9, SW1.10, SW1.11, SW1.12, SW1.13, SW1.14, SW1.15, SW1.16, U1.14 (VCC), U2.14 (VCC), U3.16 (VCC), U4.7 (CEP), U4.9 (~PE), U4.10 (CET), U4.16 (VCC), U5.14 (VCC), U6.10 (DS), U6.16 (VCC), U7.10 (~SRCLR), U7.16 (VCC), U8.20 (VCC), U9.20 (VCC), U10.1 (~R), U10.4 (~S), U10.10 (~S), U10.13 (~R), U10.14 (VCC), U11.14 (VCC), U12.14 (VCC), U13.1 (~R), U13.4 (~S), U13.10 (~S), U13.13 (~R), U13.14 (VCC), U16.3 (VI), X1.14 (Vcc)
~CLKSTART: U1.5, U11.3
~CLKSTOP: U1.1, U1.8
~CLK: U1.11, U6.2 (CP), U7.12 (RCLK)
~CS: R11.1, U5.8, U5.12
~PORTSEL: U2.1, U2.4, U8.19 (P=R), U9.19 (CE)
~PULSE: U3.11 (O1), U11.2
~RD: J2.B14 (~IOR), U2.2
~RQ_SER_RD: U3.4 (O0), U11.4
~SDCS_RESET: U3.7 (O3), U5.13
~SDCS_SET: U3.6 (O2), U5.9
~SDOUT_RESET: U3.9 (O3), U5.5
~SDOUT_SET: U3.10 (O2), U5.1
~SER_RD_AND_PULSE: U3.5 (O1), U10.2 (D), U11.5, U11.10
~SER_RD: U7.13 (~OE), U9.1 (A->B), U11.6
~SER_WR: U3.12 (O0), U6.1 (~PL), U11.13, U13.2 (D)
~WR: J2.B13 (~IOW), U2.5

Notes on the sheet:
First read, then pulse, so another byte is made ready. Used for reading blocks.
SHIFT REGISTER SD -> Z80 IN REGISTER
SD CARD S/R LATCHES
out $XX0: ~{SER_WR} is pulled low, loading value into the shift register and then exchanging a byte with the SD card. out $XX1: ~{CLKSTART} is pulled low, starting the counter circuit and exchanging a byte between shift register and SD card. out $XX2: ~{SDCS_SET} is pulled low, pulling ~{CS} high, 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
On ~{CLKSTART}, this component produces exactly 8 pulses at 8MHz.
SCK
On ~{CLKSTART}, ~{MR} will be set HIGH, activating the counter.
in $XX0: ~{SER_RD} is pulled low, reading from the shift register. There is **no** exchange with the SD card. in $XX1: ~{SER_RD_AND_PULSE} is pulled low, reading from the shift register and then exchanging a byte with the SD card. in $XX2: ~{SDOUT_SET} is pulled low, pulling MISO low via a 10k resi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
Connected to SD-CARD
~{SDOUT_SET} -> MISO LOW ~{SDOUT_RESET} -> MISO HIGH
~{SDCS_SET} -> ~{CS} HIGH -> SD CARD disabled ~{SDCS_RESET} -> ~{CS} LOW -> SD CARD active
SELECTION COMPONENT
CLOCK COMPONENT
SD CARD
Buffers data bus and ensures voltage translation between LS and HC chips.
Both CEP and CET need to be high for count to be enabled.
SHIFT REGISTER Z80 -> SD OUT REGISTER

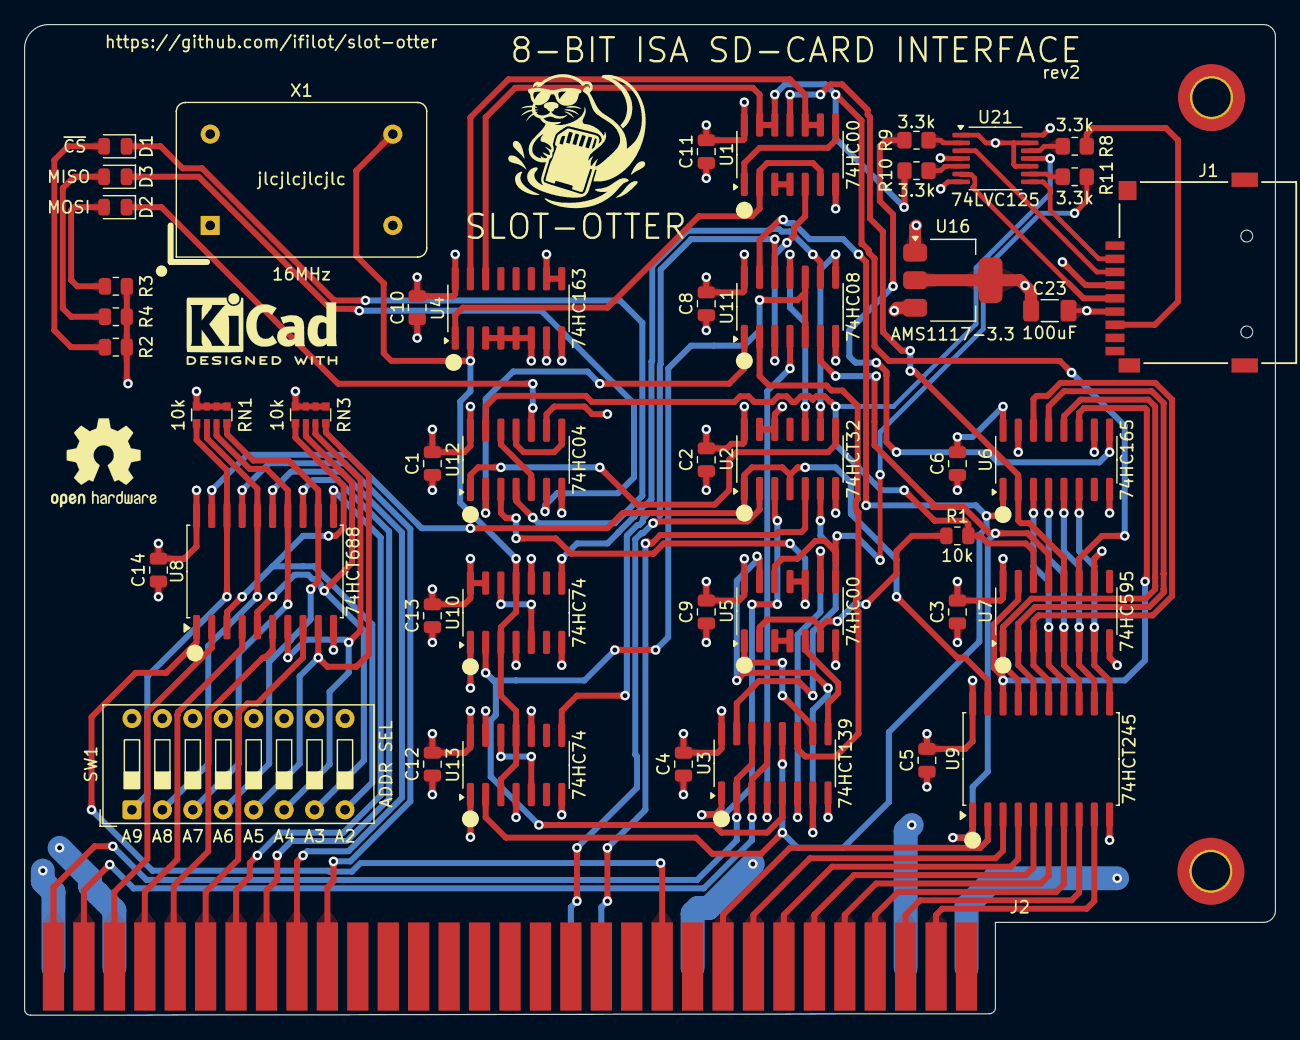
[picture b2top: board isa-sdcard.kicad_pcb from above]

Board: 4 copper layers, 104.4 x 82.7 mm, 48 parts (0 on the bottom side), 90 nets.

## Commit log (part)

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2025-10-19 Initial commit Github Actions
2025-10-19 Adjusting file
2025-10-19 Adjusting workflow file
2025-10-19 Release deployment
2025-10-19 Creating floppy images
2025-10-19 Updating README.md
2025-10-19 Adding write permission
2025-10-19 Showing files
2025-10-19 Fixing files
2025-10-19 Change verification
2025-10-19 Fixing resistor 3d file
2025-10-19 Updating README file
2025-11-03 Adding delays and improving bracket
2025-11-08 Adding colors
2025-11-15 Removing delay lines
2026-01-21 Changing max clusters to 2048
2026-01-21 Incrementing version number
2026-03-20 Fixing issue #1
2026-03-20 Adding box around create folder pane
2026-03-20 Colorizing OK for file transfer
2026-03-20 Compile on develop
2026-03-21 Adding screenshot
2026-03-21 Copying source files to floppy images
2026-03-21 Incrementing version
2026-03-21 Adding labels
2026-03-21 Adding tags
2026-03-21 Add INI-based base port config, settings dialog, and help screen
2026-03-21 Restore DOS CRLF line endings in updated source files
2026-03-21 Restore DOS CRLF line endings in updated source files (#5)
2026-03-21 Expanding explanation and polishing settings interface
2026-03-21 Increasing maximum number of files per folder
2026-06-13 Fixing files for MSDOS
2026-06-13 Initial commit SD-CARD write routines
2026-06-14 Improving commenting and routines
2026-06-14 Tuning write cycles
2026-06-14 Improving schematic, improving sd commands and making cross-compilation more convenient
2026-06-21 Adding JLCPCB numbers
2026-06-27 Implementing folder creation
2026-06-27 Refactoring otternav and initial commit copying from HD to SD
2026-06-28 Refining CPLD card

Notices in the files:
README.md:
Hardware license
https://img.shields.io/badge/Software-GPL--3.0--or--later-blue.svg
pcb/cpld/cpld.kicad_pcb:
Hardware: CERN-OHL-S-2.0; source: github.com/ifilot/slot-otter
